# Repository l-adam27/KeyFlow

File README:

KeyFlow  —  custumizable keypad for your favorite shortcuts

Built for faster workflow and maximum productivity

---

Main:

Keyflow is a small macropad, that I designed to give the user the fastest ways to control his enviroment

---

Standart layout:

> Important:
> The key mapping listed below is the fabric standart, a future software will be implemented soon

KeyMapping:

KEY 1 - SCREENSHOT
KEY 2 - MEDIA CONTROL
KEY 3 - LOCK SCREEN
KEY 4 - FOCUS MODE
KEY 5 - CLEAN DESKTOP
KEY 6 - MICROFONE MUTE

----

Rotary Encoder (Knob):

- Rotate: Volume + / Volume -
- Press: Audio mute / unmute

---

Attachments:

- PCB

- Schematic

- 3D case render

- Assembly preview

---

BOM:

Components:

Seeed XIAO RP2040 | 1x
Mechanical switches | 6x
EC11 Rotary Encoder* | 1x
Custom PCB | 1x
3D PARTS | 1x

*: (With the push thing)

---

Special Thanks:
* HackClub community for doing its thing
* Shadow & zsharpminor for reviewing the project and helping me build it better
* My dad
* My mom
* My dog
* The rubber duck standing at my desk

--

IMPORTANT:
** NOTE: I though I didnt need to write this here, but for insistence I needed to. I re-writted the entire document in portuguese. AI was used to translate parts of this document. Please be aware not evryone has the resources to fluent in englis **

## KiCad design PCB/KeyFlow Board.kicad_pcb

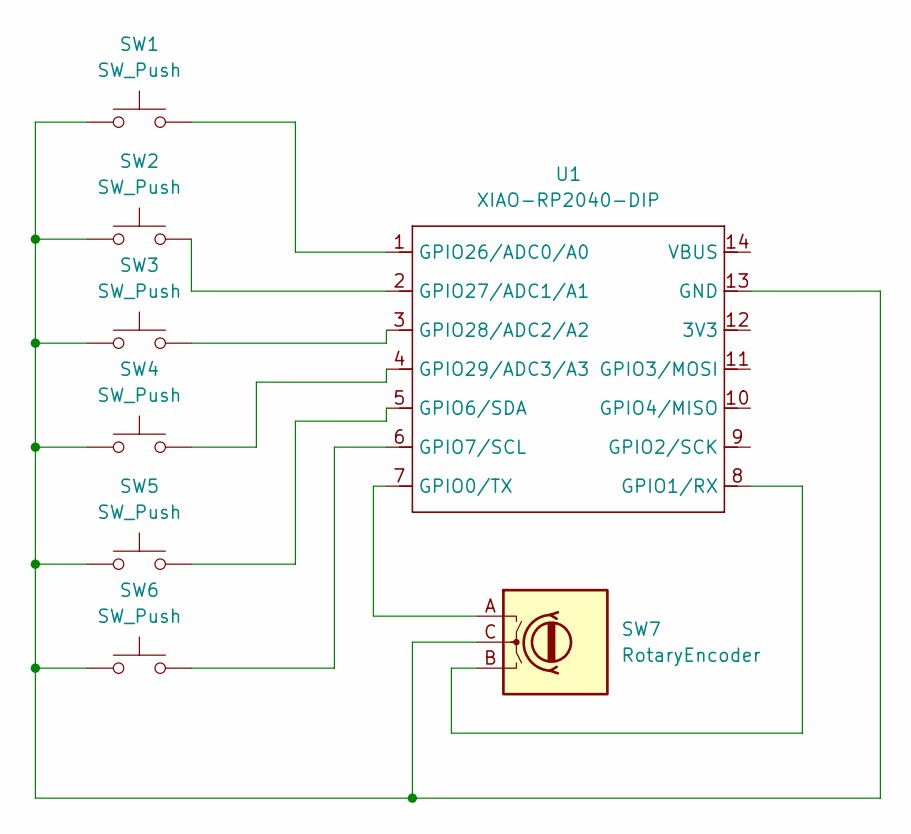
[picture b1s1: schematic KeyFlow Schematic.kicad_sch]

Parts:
SW1, SW2, SW3, SW4, SW5, SW6: SW_Push; SW_Cherry_MX_1.00u_PCB
SW7: RotaryEncoder; RotaryEncoder_Alps_EC11E-Switch_Vertical_H20mm_MountingHoles
U1: XIAO-RP2040-DIP; XIAO-RP2040-SMD

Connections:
unnamed: SW1.1, SW2.1, SW3.1, SW4.1, SW5.1, SW6.1, SW7.C, U1.13 (GND)
unnamed: SW7.A, U1.7 (GPIO0/TX)
unnamed: SW7.B, U1.8 (GPIO1/RX)
unnamed: SW5.2, U1.5 (GPIO6/SDA)
unnamed: SW6.2, U1.6 (GPIO7/SCL)
unnamed: SW1.2, U1.1 (GPIO26/ADC0/A0)
unnamed: SW2.2, U1.2 (GPIO27/ADC1/A1)
unnamed: SW3.2, U1.3 (GPIO28/ADC2/A2)
unnamed: SW4.2, U1.4 (GPIO29/ADC3/A3)

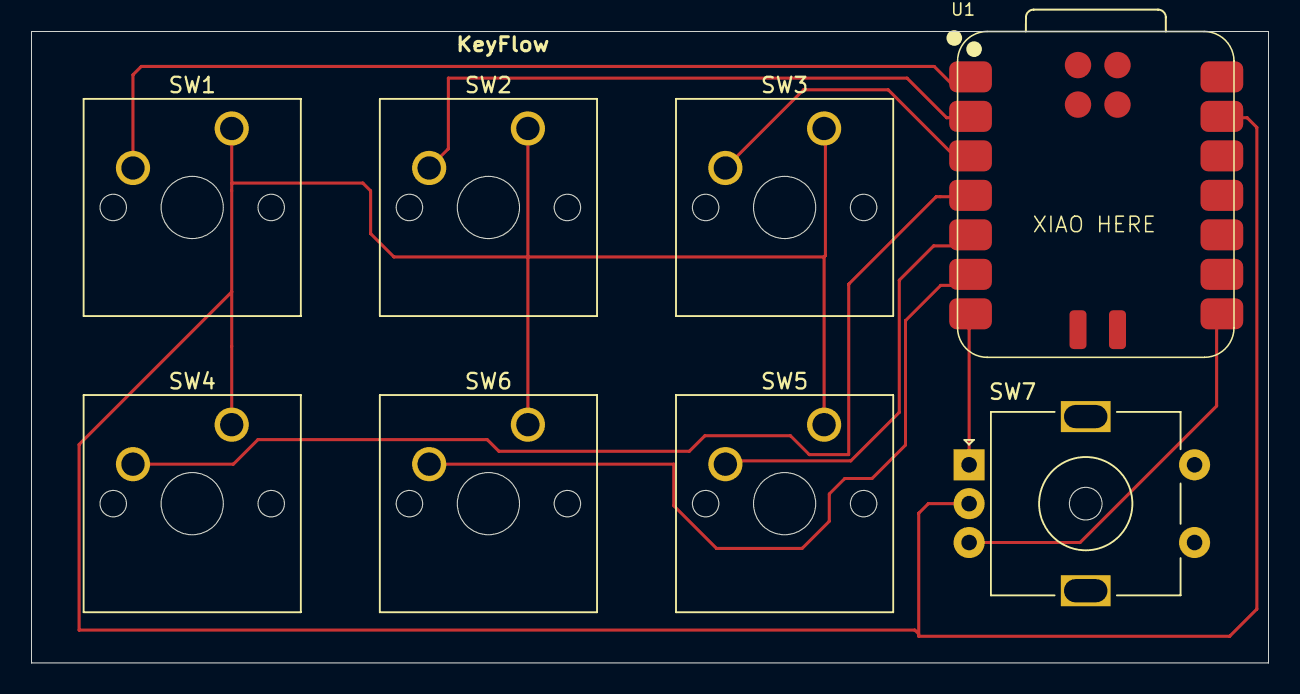
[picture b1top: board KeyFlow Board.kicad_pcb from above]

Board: 2 copper layers, 79.6 x 40.6 mm, 8 parts (0 on the bottom side), 9 nets.

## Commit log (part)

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2025-12-27 added inspiration and challenges sections
    Added sections for inspiration and challenges faced during the project.
2026-01-09 Add MIT License to the project
2026-01-09 Revise README for KeyFlow project details
    Updated README to provide detailed project overview, features, customization options, and project structure.
2026-01-09 Add images to README for project components
    Added images for PCB layout, schematic, 3D case render, and assembly preview.
2026-01-09 Update assembly preview image in README
    Replaced the assembly preview image with a new one.
2026-01-09 Remove unnecessary thhings from README
2026-01-09 Update README to remove placeholder for screenshots
    Removed placeholder text for screenshots section.
2026-01-16 Primeiro envio
2026-01-19 Add CAD, PCB and Firmware folders
2026-01-19 Revise README with file structure and images
    Updated file structure and added new images to README.
2026-01-22 Revise README for clarity and corrections
    Updated README to improve clarity and fix typos.
    Recreated without AI
2026-01-22 Remove emoji from Rotary Encoder section
2026-01-22 Add CAD STEP files
2026-01-22 Update file names in README for KeyFlow directory
2026-01-22 Add README (again)
    Added detailed information about KeyFlow, including key mappings, rotary encoder functions, attachments, BOM, and special thanks for the reviwers
2026-01-22 Added README
2026-01-22 Add README for KeyFlow customizable keypad
    Added detailed documentation for KeyFlow customizable keypad, including key mappings, rotary encoder functions, components, and special acknowledgments.
2026-01-22 Rename README to README.md
2026-01-22 Fix formatting and update key mapping section
2026-01-22 Clean PCB backups, update schematic, add gitignore
2026-01-22 Fix formatting of key mapping section in README
2026-01-22 Readme done
2026-03-31 Solve the problem
2026-04-01 Replaced CAD/KEYFLOW_Assemble_Final.step
2026-04-01 Revise README with new images and acknowledgments
    Updated images and acknowledgments in the README file. Added new images for the 3D case render and assembly preview, and revised the special thanks section for clarity.
2026-04-26 Fix typo in README heading
